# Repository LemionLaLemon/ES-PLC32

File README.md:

# ES-PLC32
The ES-PLC32 is an affordable programmable logic computer with four digital inputs, two analog inputs, and four outputs.
> [!WARNING]
> The ES-PLC32 is not [IEC 61131](https://en.wikipedia.org/wiki/IEC_61131) compliant.

## Digital Inputs
The four digital inputs should be able to handle up to 24v at 20mA but realistically should be used at 3.3v or 5v. The inputs are electrically isolated from the ESP32 via the pc817 optocoupler.

## Analog Inputs
The analog inputs are insanely dangerous to use. It is only able to handle 3.3v-5v and is absolutely not electrically isolated from the ESP32, so any power you push in through that input, will go through two resistors to divide the 5v to 3.3v (or 3.3v to 1v ish) and then directly to the ESP32. (this will be resolved in a later iteration)

## Outputs
The outputs are purely digital and can be used to drive pumps, turn on lights, open motorized valves, and such. There are no analog outputs to keep it affordable.

## Screen and buttons
The 0.96" 128x64 OLED display can be used to change setpoints for anything, view variables live, to restart the program, or start/stop hosting the programming interface, and show the ip for the programming interface.

## Software
The ES-PLC32 uses [OpenPLC](https://autonomylogic.com/) to program in ladder logic (and other languages) and to upload the program to the ES-PLC32. It is recommended to use functional block diagram rather than ladder logic as OpenPLC seems to hate ladder logic a lot.

It has inbuilt support for the ESP32-S3 by default and can upload code to it perfectly fine with no issues.

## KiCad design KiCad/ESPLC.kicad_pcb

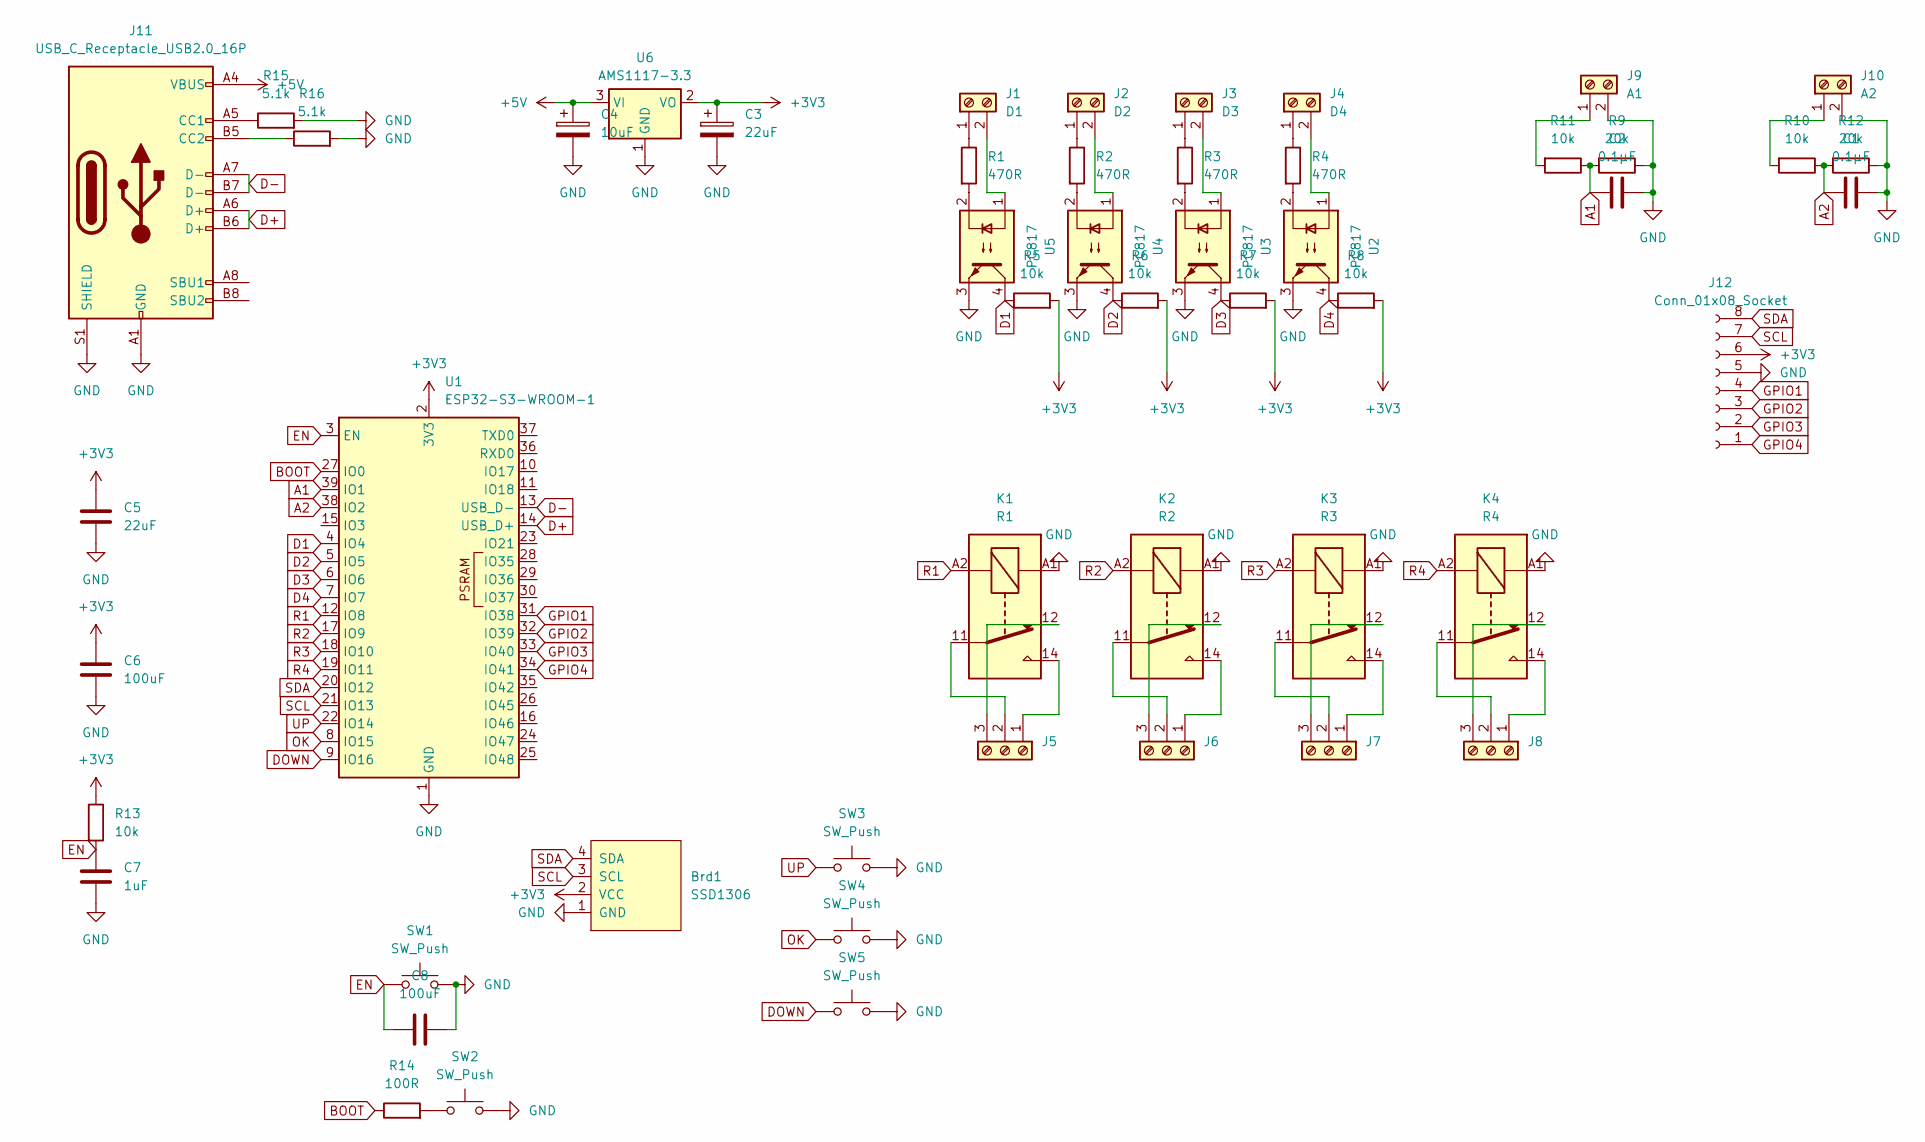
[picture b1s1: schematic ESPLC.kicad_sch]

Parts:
Brd1: SSD1306; 128x64OLED
C1, C2: 0.1μF; C_Disc_D5.0mm_W2.5mm_P5.00mm
C3: 22uF; CP_Radial_D5.0mm_P2.50mm
C4: 10uF; CP_Radial_D5.0mm_P2.50mm
C5: 22uF; C_Disc_D5.0mm_W2.5mm_P5.00mm
C6, C8: 100uF; C_Disc_D5.0mm_W2.5mm_P5.00mm
C7: 1uF; C_Disc_D5.0mm_W2.5mm_P5.00mm
J1: D1; TerminalBlock-1x2-5.08mm-with3d
J2: D2; TerminalBlock-1x2-5.08mm-with3d
J3: D3; TerminalBlock-1x2-5.08mm-with3d
J4: D4; TerminalBlock-1x2-5.08mm-with3d
J5, J6, J7, J8: Screw_Terminal_01x03; 1x3
J9: A1; TerminalBlock-1x2-5.08mm-with3d
J10: A2; TerminalBlock-1x2-5.08mm-with3d
J11: USB_C_Receptacle_USB2.0_16P; USB_C_Receptacle_GCT_USB4105-xx-A_16P_TopMnt_Horizontal
J12: Conn_01x08_Socket; PinSocket_1x08_P2.00mm_Horizontal
K1: R1; Relay_SPDT_Hongfa_JQC-3FF_0XX-1Z
K2: R2; Relay_SPDT_Hongfa_JQC-3FF_0XX-1Z
K3: R3; Relay_SPDT_Hongfa_JQC-3FF_0XX-1Z
K4: R4; Relay_SPDT_Hongfa_JQC-3FF_0XX-1Z
R1, R2, R3, R4: 470R; R_Axial_DIN0207_L6.3mm_D2.5mm_P7.62mm_Horizontal
R5, R6, R7, R8, R10, R11: 10k; R_Axial_DIN0207_L6.3mm_D2.5mm_P7.62mm_Horizontal
R9, R12: 20k; R_Axial_DIN0207_L6.3mm_D2.5mm_P7.62mm_Horizontal
R13: 10k; R_0805_2012Metric
R14: 100R; R_0805_2012Metric
R15, R16: 5.1k; R_0805_2012Metric
SW1, SW2: SW_Push; SW_PUSH_1P1T_6x3.5mm_H5.0_APEM_MJTP1250
SW3, SW4, SW5: SW_Push; SW_PUSH_6mm_H5mm
U1: ESP32-S3-WROOM-1
U2, U3, U4, U5: PC817; DIP-4_W7.62mm
U6: AMS1117-3.3; SOT-223-3_TabPin2

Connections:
+3V3: Brd1.2 (VCC), C3.1, C5.1, C6.1, J12.6, R5.2, R6.2, R7.2, R8.2, R13.1, U1.2 (3V3), U6.2 (VO)
+5V: C4.1, J11.A4 (VBUS), J11.A9 (VBUS), J11.B4 (VBUS), J11.B9 (VBUS), U6.3 (VI)
A1: C2.1, R9.2, R11.1, U1.39 (IO1)
A2: C1.1, R10.1, R12.2, U1.38 (IO2)
BOOT: R14.1, U1.27 (IO0)
D1: R5.1, U1.4 (IO4), U5.4
D2: R6.1, U1.5 (IO5), U4.4
D3: R7.1, U1.6 (IO6), U3.4
D4: R8.1, U1.7 (IO7), U2.4
D+: J11.A6 (D+), J11.B6 (D+), U1.14 (USB_D+)
D-: J11.A7 (D-), J11.B7 (D-), U1.13 (USB_D-)
DOWN: SW5.1, U1.9 (IO16); also elsewhere on the board
EN: C7.1, C8.1, R13.2, SW1.1, U1.3 (EN)
GND: Brd1.1 (GND), C1.2, C2.2, C3.2, C4.2, C5.2, C6.2, C7.2, C8.2, J9.2, J10.2, J11.A1 (GND), J11.A12 (GND), J11.B1 (GND), J11.B12 (GND), J11.S1 (SHIELD), J12.5, K1.A1, K2.A1, K3.A1, K4.A1, R9.1, R12.1, R15.2, R16.2, SW1.2, SW2.2, SW3.2, SW4.2, SW5.2, U1.1 (GND), U1.40 (GND), U1.41 (GND), U2.3, U3.3, U4.3, U5.3, U6.1 (GND); also elsewhere on the board
GPIO1: J12.4, U1.31 (IO38)
GPIO2: J12.3, U1.32 (IO39)
GPIO3: J12.2, U1.33 (IO40)
GPIO4: J12.1, U1.34 (IO41)
unnamed: J1.1, R1.1
unnamed: J1.2, U5.1
unnamed: J2.1, R2.1
unnamed: J2.2, U4.1
unnamed: J3.1, R3.1
unnamed: J3.2, U3.1
unnamed: J4.1, R4.1
unnamed: J4.2, U2.1
unnamed: J5.1, K1.14
unnamed: J5.2, K1.11
unnamed: J5.3, K1.12
unnamed: J6.1, K2.14
unnamed: J6.2, K2.11
unnamed: J6.3, K2.12
unnamed: J7.1, K3.14
unnamed: J7.2, K3.11
unnamed: J7.3, K3.12
unnamed: J8.1, K4.14
unnamed: J8.2, K4.11
unnamed: J8.3, K4.12
unnamed: J9.1, R11.2
unnamed: J10.1, R10.2
unnamed: J11.A5 (CC1), R15.1
unnamed: J11.B5 (CC2), R16.1
unnamed: R1.2, U5.2
unnamed: R2.2, U4.2
unnamed: R3.2, U3.2
unnamed: R4.2, U2.2
unnamed: R14.2, SW2.1
OK: SW4.1, U1.8 (IO15); also elsewhere on the board
R1: K1.A2, U1.12 (IO8)
R2: K2.A2, U1.17 (IO9)
R3: K3.A2, U1.18 (IO10)
R4: K4.A2, U1.19 (IO11)
SCL: Brd1.3 (SCL), J12.7, U1.21 (IO13)
SDA: Brd1.4 (SDA), J12.8, U1.20 (IO12)
UP: SW3.1, U1.22 (IO14); also elsewhere on the board

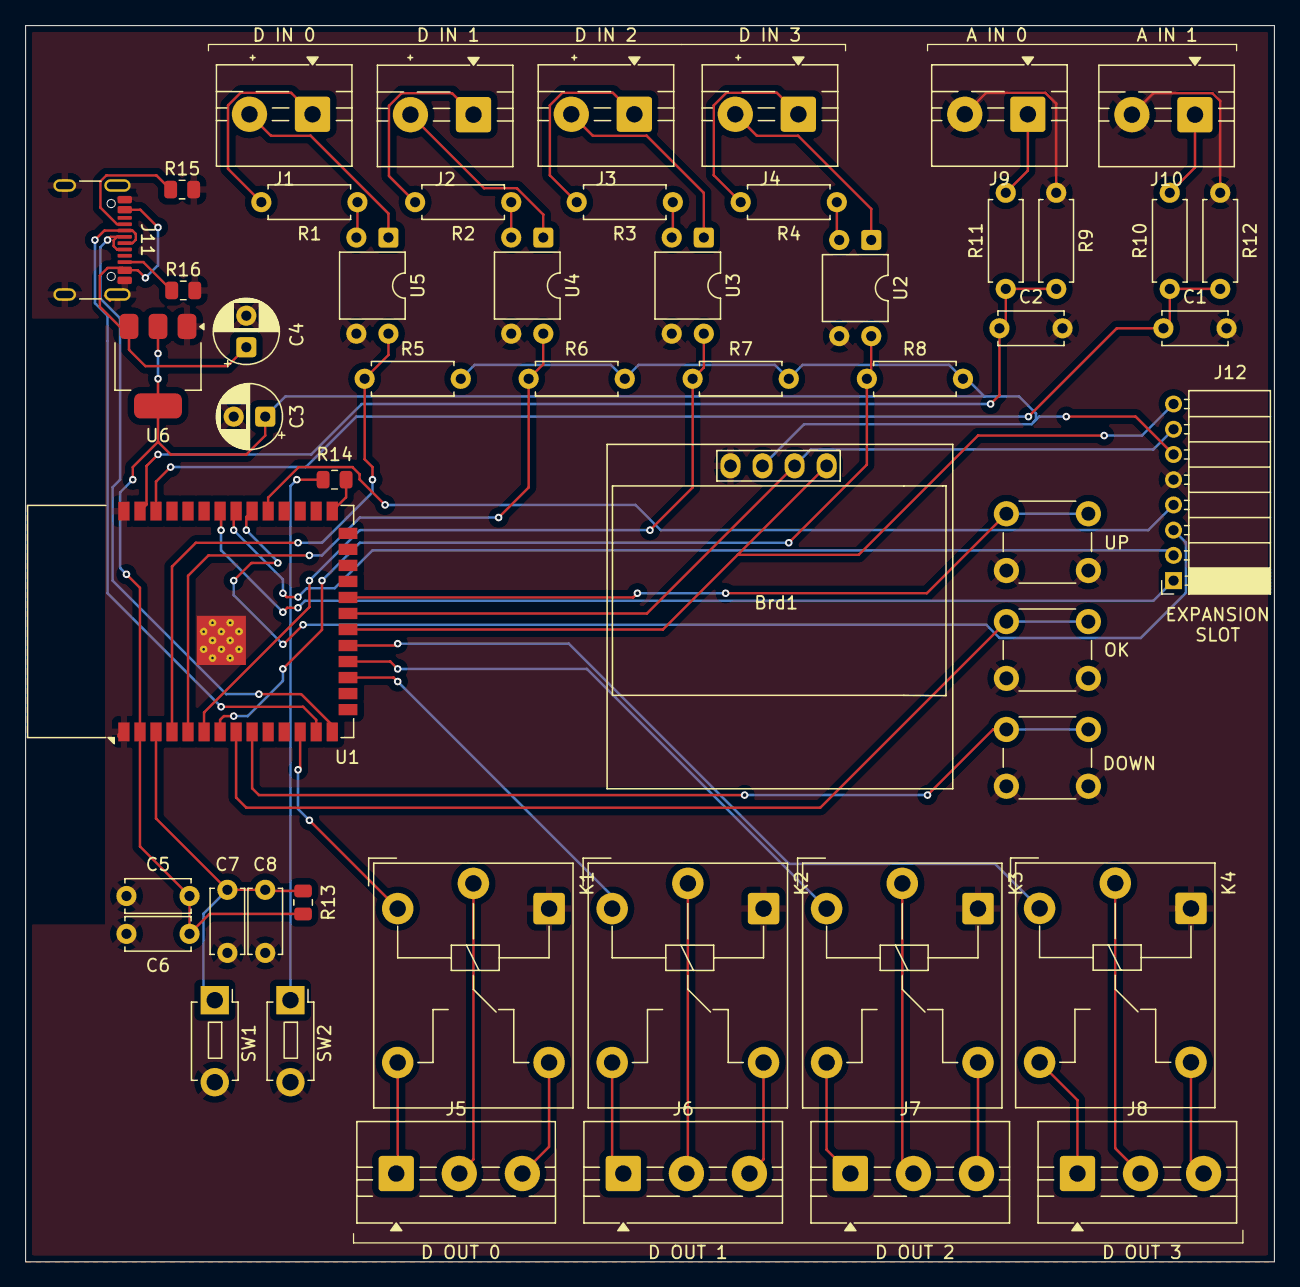
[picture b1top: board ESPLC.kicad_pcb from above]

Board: 2 copper layers, 99.0 x 98.0 mm, 52 parts (0 on the bottom side), 55 nets.

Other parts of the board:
DOWN: SW_Push; SW_PUSH_6mm_H5mm
OK: SW_Push; SW_PUSH_6mm_H5mm
UP: SW_Push; SW_PUSH_6mm_H5mm

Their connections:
DOWN: DOWN.1; also elsewhere on the board
GND: DOWN.2, OK.2, UP.2; also elsewhere on the board
OK: OK.1; also elsewhere on the board
UP: UP.1; also elsewhere on the board

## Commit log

2026-04-05 added README.md
2026-04-05 Added BOM
2026-04-05 Added Software section to README, updated Gerber
2026-06-25 Updated readme or clarity and safety warnings
    Reworded some stuff, added the IEC 61131 noncompliance warning
